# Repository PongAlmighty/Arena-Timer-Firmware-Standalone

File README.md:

# Arena Timer Firmware

A professional countdown timer system for competitive arenas, combat sports, and event timing. Built on the Waveshare RP2040-Zero with a vibrant 64x32 RGB LED matrix display, web-based control, and seamless integration with [FightTimer](https://github.com/PongAlmighty/FightTimer) by PongAlmighty.

## Features

### Display & Visual Customization
- **64x32 RGB LED Matrix** with full color control
- **Dynamic Color Thresholds** - automatically change colors as time decreases
- **Multiple Font Choices** - Sans, Serif, Monospace, Retro/Pixel styles
- **Adjustable Brightness** - 0-255 levels for any lighting condition
- **Character Spacing Control** - fine-tune text appearance
- **Display Rotation** - flip orientation 180° with one button

### Timer Controls
- **Countdown Mode** - configurable duration up to 60 minutes
- **Start/Pause/Reset** - full manual control
- **Sub-Second Precision** - displays tenths of seconds under 1 minute
- **Visual States** - blinking when paused, flashing when expired

### Web Interface
- **Responsive Three-Column Layout** - Timer controls, color settings, system status
- **Real-Time Console** - live event logging with timestamps
- **Live Updates** - automatic status refresh and button state management
- **Mobile Friendly** - works on phones, tablets, and desktops

### Network & Integration
- **DHCP Support** with static IP fallback (10.0.0.21)
- **mDNS Hostname** - access via `http://arenatimer.local`
- **FightTimer Integration** - Socket.IO connection for synchronized timing (credit: [PongAlmighty](https://github.com/PongAlmighty/))
- **RESTful API** - control timer programmatically

## Hardware

### Required Components
- **Silicognition RP2040-Shim** microcontroller
  - Designed to solder directly to the HUB75 input header on the back of the matrix
  - Provides integrated power regulation (5V to 3.3V)
- **64x32 RGB LED Matrix Panel** (HUB75 interface, P5 pitch recommended)
- **W5500 Ethernet Module** (SPI interface, PoE-FeatherWing or compatible)
- **5V Power Supply** (minimum 2A, 4A recommended for full brightness / more pixels)
  - I used a 5V 20W PoE splitter mounted to the back of the enclosure

### Pin Configuration

**Important:** This firmware uses a specific pin mapping optimized for the RP2040-Shim mounting directly to the HUB75 header. The Ethernet module uses SPI1 to avoid conflicts with the Matrix control signals.

#### RP2040-Shim GPIO Pinout

| RP2040 GPIO | Function | Peripheral | Shim Label | Notes |
|-------------|----------|------------|------------|-------|
| **GPIO 0** | Output Enable (OE) | Matrix | TX | Active low |
| **GPIO 1** | Latch (LAT) | Matrix | RX | |
| **GPIO 6** | Red Data 2 (R2) | Matrix | D4 | Bottom half |
| **GPIO 10** | SPI Clock | Ethernet | SCK | SPI1 |
| **GPIO 11** | SPI MOSI | Ethernet | MOSI | SPI1 |
| **GPIO 12** | SPI MISO | Ethernet | MISO | SPI1 |
| **GPIO 16** | Red Data 1 (R1) | Matrix | SDA | Top half |
| **GPIO 17** | Green Data 1 (G1) | Matrix | SCL | Top half |
| **GPIO 19** | Green Data 2 (G2) | Matrix | D6 | Bottom half |
| **GPIO 20** | Blue Data 1 (B1) | Matrix | D9 | Top half |
| **GPIO 21** | SPI Chip Select | Ethernet | D11 | CS for W5500 |
| **GPIO 22** | Matrix Clock (CLK) | Matrix | D13 | Pixel clock |
| **GPIO 25** | Blue Data 2 (B2) | Matrix | D25 | Bottom half |
| **GPIO 26** | Address D | Matrix | A3 | Row select |
| **GPIO 27** | Address C | Matrix | A2 | Row select |
| **GPIO 28** | Address B | Matrix | A1 | Row select |
| **GPIO 29** | Address A | Matrix | A0 | Row select |

> **Warning:** GPIO 24 is hardwired to VBUS sensing. Never use for I/O or the board will crash.

#### HUB75 Connector Pinout (Matrix Side)

| HUB75 Pin | Signal | RP2040 GPIO | Function |
|-----------|--------|-------------|----------|
| 1 | R1 | GPIO 16 | Red Data (Top) |
| 2 | G1 | GPIO 17 | Green Data (Top) |
| 3 | B1 | GPIO 20 | Blue Data (Top) |
| 4 | GND | - | Ground |
| 5 | R2 | GPIO 6 | Red Data (Bottom) |
| 6 | G2 | GPIO 19 | Green Data (Bottom) |
| 7 | B2 | GPIO 25 | Blue Data (Bottom) |
| 8 | GND | - | Ground |
| 9 | A | GPIO 29 | Address A |
| 10 | B | GPIO 28 | Address B |
| 11 | C | GPIO 27 | Address C |
| 12 | D | GPIO 26 | Address D |
| 13 | CLK | GPIO 22 | Pixel Clock |
| 14 | LAT | GPIO 1 | Latch |
| 15 | OE | GPIO 0 | Output Enable |
| 16 | GND | - | Ground |

> **Note:** The RP2040-Shim is powered by connecting 5V from the matrix power supply to the VUSB pin (3rd pin on right header). The onboard regulator converts this to 3.3V for logic. Do not connect USB while external 5V is applied unless using a data-only cable.

For complete wiring diagrams and PCB design files, see [wiring_connections.md](wiring_connections.md).

### Custom PCB & 3D Enclosure

**Custom PCB** is currently in production and will be added to this repository once tested and verified.

**3D Enclosure** files for a custom LED matrix enclosure are available in the `3d-models/` directory:
- `Timer Assembly v23.step` - STEP format for CAD editing
- `Timer Assembly v23.f3z` - Fusion 360 archive format

Files are print-ready and designed for:
- Standard 64x32 P5 RGB matrix panels
- RP2040-Shim direct mounting to HUB75 header
- PoE splitter bracket mount

## Quick Start

### 1. Flash Firmware
```bash
pio run --target upload
```

### 2. Network Connection
The timer will attempt DHCP, then fall back to `10.0.0.21` if unavailable. The assigned IP displays on the matrix for 5 seconds at startup.

### 3. Web Interface
Access the control panel at:
- `http://arenatimer.local` (mDNS)
- `http://[IP_ADDRESS]` (direct)

Use the web interface to:
- Start, pause, and reset the timer
- Set duration (minutes and seconds)
- Configure color thresholds for time-based alerts
- Adjust display settings (font, brightness, letter spacing)
- Flip display orientation
- Monitor system status and event logs

### 4. FightTimer Integration
To connect with FightTimer:
1. Ensure FightTimer is running on your network
2. In the **WebSocket Connection** section, enter:
   - **Host**: IP address of the computer running FightTimer
   - **Port**: `8765` (default Socket.IO port)
   - **Path**: `/socket.io/`
3. Click **Connect**

The timer will automatically sync with FightTimer's start/stop/reset commands and duration settings.

**What Gets Synchronized:**
- ✅ Timer start/stop/reset commands
- ✅ Duration changes
- ✅ Time remaining updates
- ✅ Expired/paused states

FightTimer sends `timer_update` events via Socket.IO that control the Arena Timer display.

**Alternative connection methods:**

Via code in `src/main.cpp`:
```cpp
void setup() {
    // ... existing setup code ...
    wsClient->connect("192.168.1.100", 8765, "/socket.io/");
}
```

Via API endpoint:
```bash
curl -X POST "http://arenatimer.local/api/websocket/connect" \
  -d "host=192.168.1.100&port=8765&path=/socket.io/"
```

## Configuration

### Network Settings
Edit `src/main.cpp` to change network defaults:
```cpp
uint8_t mac[] = {0xDE, 0xAD, 0xBE, 0xEF, 0xFE, 0xED};  // MAC address
uint8_t static_ip[] = {10, 0, 0, 21};                   // Static IP fallback
const char* hostname = "arenatimer";                     // mDNS hostname
```

### Display Settings
Configure default display settings in `src/main.cpp`:
```cpp
// Set default font
timerDisplay.setFont(&FreeSansBold12pt7b);

// Set default duration (hours, minutes, seconds)
timerDisplay.getTimer().setDuration({0, 3, 0});  // 3 minutes

// Color thresholds (set via web interface or programmatically)
timerDisplay.addColorThreshold(120, 255, 255, 0);  // Yellow at 2 minutes
timerDisplay.addColorThreshold(60, 255, 0, 0);     // Red at 1 minute
```

### Available Fonts
- **Sans**: `FreeSans9pt7b`, `FreeSans12pt7b`, `FreeSansBold9pt7b`, `FreeSansBold12pt7b`
- **Serif**: `FreeSerif9pt7b`, `FreeSerif12pt7b`, `FreeSerifBold9pt7b`, `FreeSerifBold12pt7b`
- **Mono**: `FreeMono9pt7b`, `FreeMono12pt7b`, `FreeMonoBold9pt7b`, `FreeMonoBold12pt7b`
- **Retro**: `Org_01`, `Picopixel`, `TomThumb` (ultra-compact pixel fonts)
- **Custom**: `Aquire_BW0ox12pt7b`, `AquireBold_8Ma6012pt7b`, `AquireLight_YzE0o12pt7b`

### Pin Configuration
Default pins are defined in `include/RGBMatrix.h` for the Waveshare RP2040-Zero. Modify if using different pin connections.

### Performance Optimization
The firmware includes debug flags that can be disabled for optimal timing performance:

```cpp
// src/main.cpp
#define DEBUG_MAIN false

// src/WebServer.cpp
#define DEBUG_WEBSERVER false

// src/WebSocketClient.cpp
#define DEBUG_WEBSOCKET false
```

When all debug flags are `false`, Serial output is disabled, eliminating timing delays. This is recommended for production use.

## API Reference

The timer exposes a RESTful API for programmatic control:

### Timer Control
```bash
# Start timer
POST /api?action=start

# Pause timer
POST /api?action=pause

# Reset timer
POST /api?action=reset

# Flip display orientation
POST /api?action=flip
```

### Settings
```bash
# Update timer settings
POST /api?action=settings&duration=180&font=4&spacing=3&brightness=255

# Update color thresholds
POST /api/thresholds
Content-Type: application/x-www-form-urlencoded
thresholds=120:%23FFFF00|60:%23FF0000&default=%2300FF00
```

### Status Information
```bash
# Get timer status
GET /api/status

# Get network information
GET /api/network/status

# Get WebSocket connection status
GET /api/websocket/status
```

### WebSocket Connection
```bash
# Connect to FightTimer
POST /api/websocket/connect
Content-Type: application/x-www-form-urlencoded
host=192.168.1.100&port=8765&path=/socket.io/

# Disconnect
POST /api/websocket/disconnect
```

## Troubleshooting

### Display Issues
- **Blank display**: Check power supply (5V, minimum 2A recommended)
- **Corrupted display**: Verify HUB75 cable connections
- **Wrong colors**: Check RGB pin mappings in `src/RGBMatrix.cpp`

### Network Issues
- **Can't access web interface**: Check Ethernet cable, verify IP on display at startup
- **DHCP not working**: Timer falls back to static IP `10.0.0.21`
- **mDNS not resolving**: Try direct IP address instead

### FightTimer Connection
- **Won't connect**: Verify FightTimer is running and accessible at the specified host/port
- **Connects but no updates**: Check that FightTimer is sending `timer_update` Socket.IO events
- **Frequent disconnects**: Check network stability between devices

## Development

### Build Environment
- **Framework**: Arduino
- **Platform**: Raspberry Pi Pico (RP2040)
- **Tool**: PlatformIO

### Key Libraries
- **Adafruit Protomatter** - RGB matrix driver
- **Ethernet** - W5500 network interface
- **WebSockets** - Socket.IO client (links2004/arduinoWebSockets)
- **EthernetBonjour** - mDNS support

### Building from Source
```bash
# Clone repository
git clone https://github.com/EVAC-AZ/Arena-Timer-Firmware.git
cd Arena-Timer-Firmware

# Install dependencies
pio pkg install

# Build and upload
pio run --target upload

# Monitor serial output (optional)
pio device monitor
```

### Project Structure
```
arena-timer-firmware/
├── src/
│   ├── main.cpp              # Entry point and configuration
│   ├── Timer.cpp             # Core timer logic
│   ├── TimerDisplay.cpp      # LED matrix display control
│   ├── RGBMatrix.cpp         # Low-level matrix driver
│   ├── WebServer.cpp         # Web server and API
│   └── WebSocketClient.cpp   # Socket.IO client
├── include/
│   ├── Timer.h
│   ├── TimerDisplay.h
│   ├── RGBMatrix.h
│   ├── WebServer.h
│   ├── WebSocketClient.h
│   └── CustomFonts/          # Custom font definitions
├── 3d-models/                # Enclosure models
├── docs/                     # Documentation
├── platformio.ini            # Build configuration
└── README.md
```

### Future Plans
A standalone Arduino/PlatformIO library is planned to simplify integration of this timer system into other projects. The goal is to separate the timing/web UI/FightTimer integration code from the hardware-specific code, allowing use with different display hardware and microcontrollers (ESP32, ESP8266, etc.).

## Credits

- **FightTimer Integration**: [PongAlmighty/FightTimer](https://github.com/PongAlmighty/FightTimer) - Synchronized timing system for combat sports
- **RGB Matrix Control**: Adafruit Protomatter library
- **WebSocket Library**: Arduino WebSockets by links2004
- **Enclosure Design**: EVAC-AZ

## License

This project is open source. See `LICENSE` for details.

## Contributing

Contributions are welcome! Please:
1. Fork the repository
2. Create a feature branch
3. Make your changes with clear commits
4. Submit a pull request

For bug reports and feature requests, open an issue on GitHub.

---

**Built for arena timing excellence** 🏆

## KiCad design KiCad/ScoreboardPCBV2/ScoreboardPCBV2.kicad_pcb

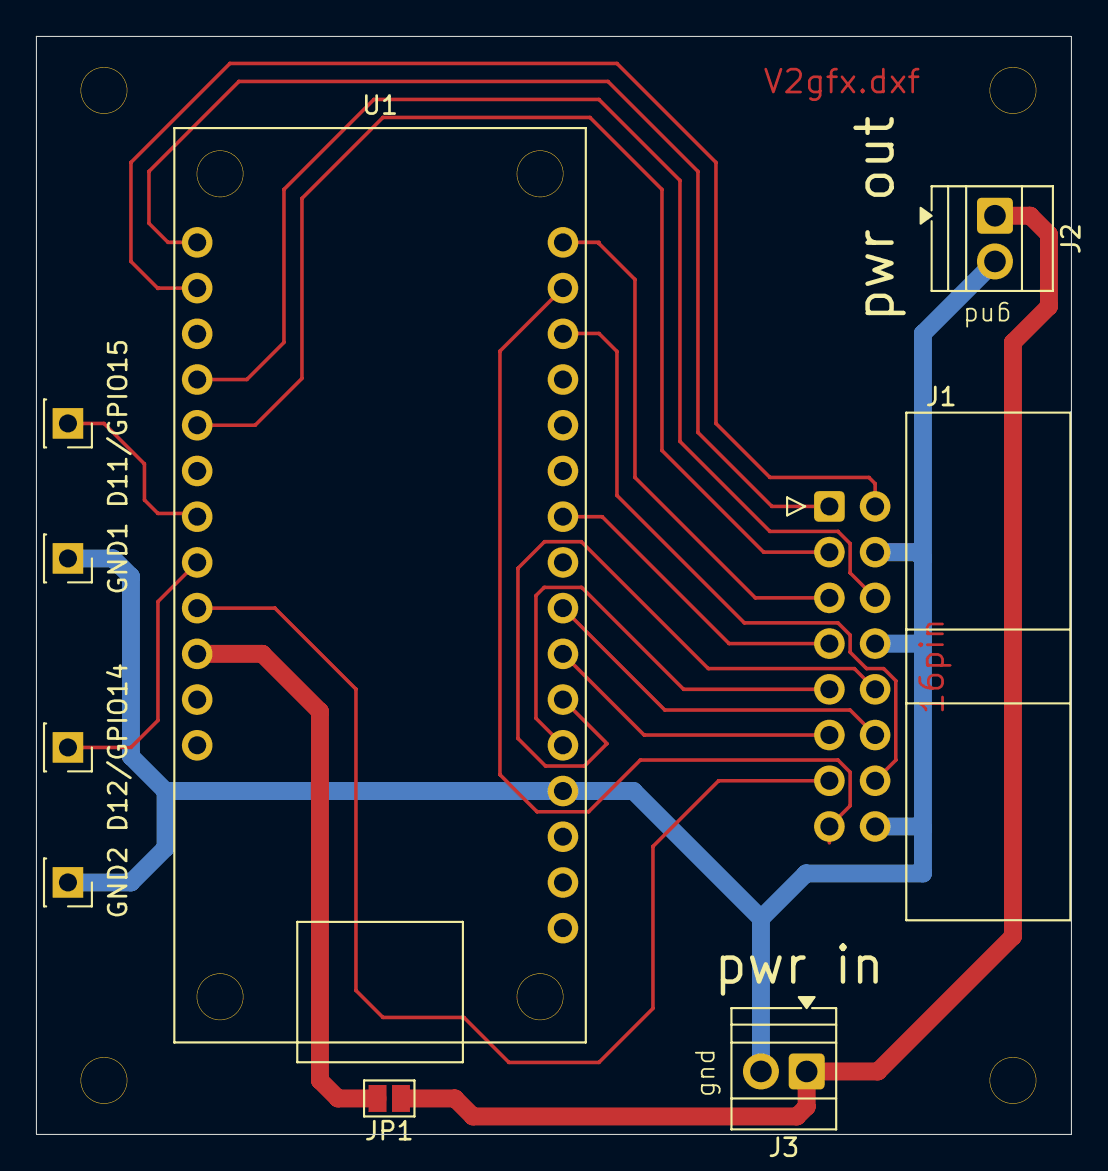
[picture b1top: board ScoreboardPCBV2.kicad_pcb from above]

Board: 2 copper layers, 57.5 x 61.0 mm, 9 parts (0 on the bottom side), 18 nets.

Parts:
D11/GPIO15: D11/GPIO15; PinSocket_1x01_P2.54mm_Vertical
D12/GPIO14: D12/GPIO14; PinSocket_1x01_P2.54mm_Vertical
GND1, GND2: GND; PinSocket_1x01_P2.54mm_Vertical
J1: 10056844-116ALF; IDC-Header_2x08_P2.54mm_Horizontal
J2, J3: Screw_Terminal_01x02; TerminalBlock_Xinya_XY308-2.54-2P_1x02_P2.54mm_Horizontal
JP1: Bridge For POE Powah!; SolderJumper-2_P1.3mm_Open_Pad1.0x1.5mm
U1: RP2040-Shim; Adafruit-Feather-RP2040

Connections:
unnamed: J2.1, J3.1, JP1.1 (A)
unnamed: GND1.1, GND2.1, J1.4, J1.8, J1.16, J2.2, J3.2, U1.4 (GND)
unnamed: JP1.2 (B), U1.26 (VUSB)
unnamed: J1.9, U1.5 (A0/GPIO29)
unnamed: J1.10, U1.6 (A1/GPIO28)
unnamed: J1.11, U1.7 (A2/GPIO27)
unnamed: J1.12, U1.8 (A3/GPIO26)
unnamed: J1.5, U1.16 (D4/GPIO6)
unnamed: J1.6, U1.20 (D6/GPIO19)
unnamed: J1.3, U1.21 (D9/GPIO20)
unnamed: D11/GPIO15.1, U1.23 (D11/GPIO15)
unnamed: D12/GPIO14.1, U1.24 (D12/GPIO14)
unnamed: J1.13, U1.25 (D13/GPIO22)
unnamed: J1.7, U1.10 (D25/GPIO25)
unnamed: J1.14, U1.14 (RX/GPIO1)
unnamed: J1.2, U1.18 (SCL/GPIO17)
unnamed: J1.1, U1.17 (SDA/GPIO16)
unnamed: J1.15, U1.15 (TX/GPIO0)

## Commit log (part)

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2025-10-04 platformio project structure
2025-10-05 added docs, Waveshare demos, and pins header file
2025-10-08 First light! Working LED matrix demo
2025-10-10 First working draft of RGB Matrix timer with web UI
2025-10-10 fix: seconds decimal place was vertically centered, now properly bottom-aligns
2025-10-10 WIP: add custom fonts (currently missing characters)
2025-10-10 feat: websocket connection to browser-based timers
2025-10-10 Fully working websocket implementation (through helper python scripts, no direct connection yet)
2025-10-10 feat: direct socket.io websocket connection between hardware timer and FightTimer (less lag than bridge setups)
2025-10-10 feat: display brightness slider
2025-10-18 Rename Comms files to WebServer, add DHCP support, and clean up implementation as much as possible
2025-12-22 feat: Update RGB matrix pin definitions for RP2040-Shim, add a minimal test function, reorder WebServer includes, and remove a custom font.
2025-12-23 fix: Correct matrix pinout in docs and code, update SPI CS, and add raw GPIO toggle for wiring diagnosis.
2025-12-24 feat: Implement initial arena timer firmware with web server, Socket.IO client, and display control.
2025-12-25 feat: Integrate Adafruit_Protomatter library, relocate original source files to backup, and add new development utilities and documentation.
2025-12-26 currently broken
2025-12-26 feat: Implement WebServer and TimerDisplay features, and add EthernetBonjour and WebSockets library dependencies.
2025-12-27 feat: Implement persistent storage for timer display settings including duration, color thresholds, font, and letter spacing.
2025-12-27 Update submodule references to include local RP2040/W5500 fixes
2025-12-30 feat: Add physical buttons for Start, Stop/Reset, and Network Info, including their handling logic and wiring documentation.
2026-01-17 feat: Add initial KiCad schematic and symbols for the RP2040 Arena Timer with HUB75 matrix, and update firmware and documentation.
2026-05-31 fix: resolve HUB75 panel startup crash, UART conflict, and signal integrity timing
2026-05-31 chore(01-01): add thomasfredericks/Bounce2@^2.71 to platformio.ini lib_deps
    - Appended Bounce2 as last active entry in lib_deps block with 4-space indent
    - Satisfies BTN-03 requirement for debounce library declaration
2026-05-31 feat(01-01): add ButtonHandler class header (D-01, D-04, D-05, D-06)
    - #pragma once guard (not #ifndef per project convention)
    - Declares constructor ButtonHandler(uint8_t pin1, uint8_t pin2)
    - Declares begin() for hardware init in setup()
    - Declares poll() for non-blocking update in loop()
    - Private members: _pin1, _pin2, _b1, _b2 (leading underscore + snake_case)
    - No event accessors — Phase 1 scaffold only
2026-05-31 feat(01-01): implement ButtonHandler class (D-05, D-06, BTN-01, BTN-02)
    - Constructor stores pin1/pin2 only via member initializer list, no hardware work
    - begin() calls attach(pin, INPUT_PULLUP) + interval(25) for both buttons (BTN-01)
    - poll() calls _b1.update() + _b2.update() non-blocking (BTN-02)
    - DEBUG_BUTTONHANDLER=true enables serial diagnostic output for Phase 1 verification
    - No delay(), no separate pinMode(), no update() called more than once per instance
2026-05-31 docs(01-01): complete ButtonHandler foundation plan summary
    - SUMMARY.md for Phase 01 Plan 01 (BTN-01, BTN-02, BTN-03 satisfied)
    - 3 tasks committed: Bounce2 in platformio.ini, ButtonHandler.h, ButtonHandler.cpp
2026-05-31 feat(01-02): wire ButtonHandler into main.cpp (BTN-01, BTN-02)
    - Add #include "ButtonHandler.h" to project headers block
    - Add #define BTN_1 14 / BTN_2 15 to HARDWARE PIN CONFIGURATION block
    - Declare ButtonHandler buttonHandler(BTN_1, BTN_2) as file-scope global
    - Add buttonHandler.begin() in setup() as section 2 (renumber Ethernet/Network/WS/Settings to 3-6)
    - Place buttonHandler.poll() as first call in loop() before timerDisplay.update()
2026-05-31 docs(01-02): complete ButtonHandler main.cpp wiring plan
    - Summary for plan 01-02: ButtonHandler wired into main.cpp, pio run exits 0
2026-05-31 feat(02-01): implement ButtonHandler armed state machine (BTN-04, BTN-05, BTN-06)
    - Add isArmed(), startStopPressed(), stopResetPressed() public API to header
    - Add _armed, _startStopPending, _stopResetPending private members
    - Rewrite poll() with ordered state machine: reset flags, arm check, disarm on rose(), B1 routing
    - Extend constructor initializer list with _armed(false), _startStopPending(false), _stopResetPending(false)
    - Remove Phase 1 BTN1 fell / BTN2 fell diagnostics (D-12); replace with Phase 2 state messages
2026-05-31 feat(02-01): add WebSocketClient emitTimerControl stub (D-05, D-07)
    - Declare emitTimerControl(const char* action) in WebSocketClient.h public section
    - Implement at end of WebSocketClient.cpp using strcmp dispatch pattern
    - Calls _timer->start() / _timer->stop() / _timer->reset() for Phase 2 local stub
    - Phase 3 seam: prepend Socket.IO emit before local calls without renaming
2026-05-31 docs(02-01): complete ButtonHandler state machine + emitTimerControl plan
2026-05-31 feat(02-02): TimerDisplay armed overlay — setArmed() + update() short-circuit (D-09, D-10, D-11, BTN-07)
    - Added void setArmed(bool armed) public declaration to TimerDisplay.h with doxygen comment
    - Added bool _armed private member after _was_expired in TimerDisplay.h
    - Extended constructor init list with _armed(false) in TimerDisplay.cpp
    - Added setArmed() implementation with transition-aware blink state reset on both arm and disarm
    - Added armed short-circuit block at top of update(): 1Hz blink of warm yellow STOP? at x=17 y=12
    - Armed block uses _matrix.setFont(NULL) for predictable default font sizing
2026-05-31 feat(02-02): main.cpp button event routing (D-06, D-08, BTN-04, BTN-05, BTN-06)
    - Added timerDisplay.setArmed(buttonHandler.isArmed()) immediately after buttonHandler.poll()
    - Added stopResetPressed() check before startStopPressed() (chord reset takes priority)
    - stopResetPressed branch calls emitTimerControl(stop) then emitTimerControl(reset) via wsClient null-guard
    - startStopPressed branch toggles: isRunning() -> emitTimerControl(stop), else -> emitTimerControl(start)
    - timerDisplay.update() moved after all button routing per D-11 anti-pattern
    - All emitTimerControl calls wrapped in if (wsClient) null-guard
2026-05-31 docs(02-02): complete TimerDisplay armed overlay + main.cpp button event routing plan
2026-05-31 feat(03-01): add Phase 3 private sync state members to WebSocketClient.h
    - Add _suppressAction (String) for SYNC-02 echo suppression tracking
    - Add _suppressUntilMs (unsigned long) for 500ms suppression window expiry
    - Add _initialSyncPending (bool) for SYNC-03 initial connect sync detection
2026-05-31 feat(03-01): implement SYNC-01 + SYNC-02 + SYNC-03 in WebSocketClient.cpp
    - SYNC-01: emitTimerControl() sends 42["timer_control",{"action":"..."}] via
    sendTXT() before calling local timer method; offline actions skip emit
    - SYNC-02: 500ms one-shot echo suppression in handleTimerUpdate(); suppression
    window set only when connected; cleared on first matching action
    - SYNC-03: runtime start requests timer_status with {"timer_id":1}; timer_status
    branch in handleWebSocketEvent() applies time_left via setDuration+reset+start;
2026-05-31 fix: correct namespace format from /timerN to /timer/N to match FightTimer multi-timer paths
2026-05-31 revert: restore /timerN namespace format — FightTimer uses /timer1 not /timer/1
2026-06-05 Add Arena Timer integration guide (docs/INTEGRATION_GUIDE.md)
2026-06-07 Add single-file codebase bundle for Claude.ai Project context
    https://claude.ai/code/session_013BSocyPDWXguXFZsXfqScP
2026-06-07 docs: correct integration guide to match firmware behavior
    - Mark POST /api action=flip as vestigial no-op (returns success but does
    not rotate the display; orientation call is not wired up)
    - Clarify REST reset takes no params vs WebSocket reset (minutes/seconds)
    - Note pause (REST) vs stop (WebSocket) verb difference and silent-ignore
    - Document /api/status limitation: only isPaused exposed; running vs idle
    indistinguishable; no remaining-time readout (relevant to state sync)
